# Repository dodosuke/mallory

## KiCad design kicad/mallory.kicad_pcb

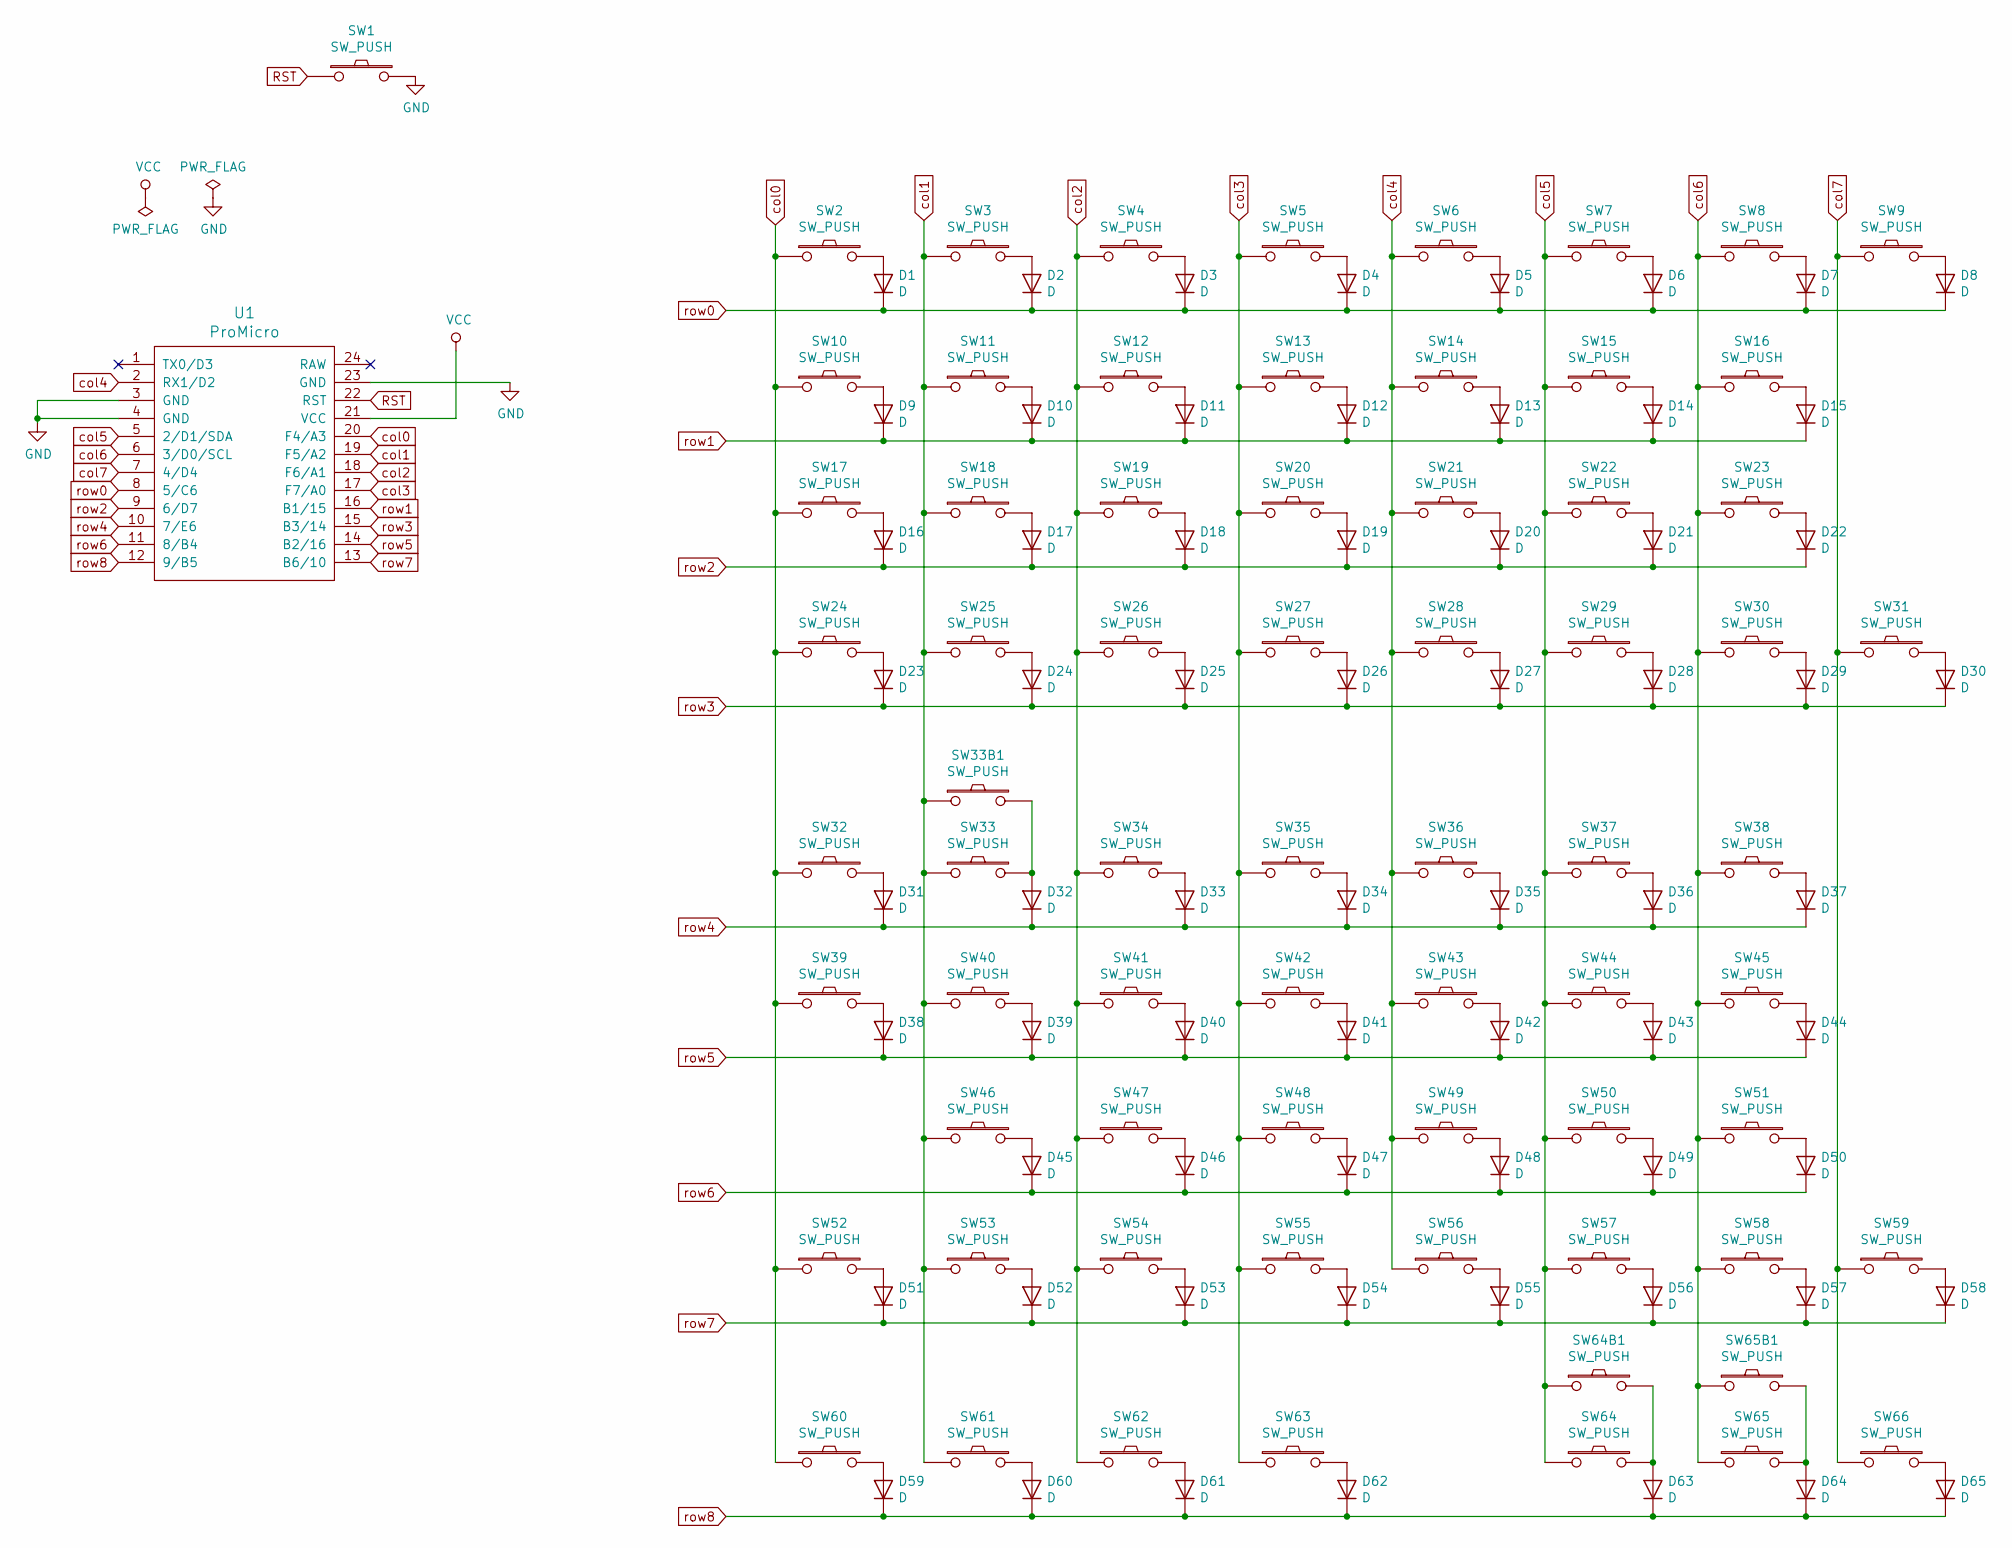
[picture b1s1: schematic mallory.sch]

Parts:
D1, D2, D3, D4, D5, D6, D7, D8, D9, D10, D11, D12, D13, D14, D15, D16, D17, D18, D19, D20, D21, D22, D23, D24, D25, D26, D27, D28, D29, D30, D31, D32, D33, D34, D35, D36, D37, D38, D39, D40, D41, D42, D43, D44, D45, D46, D47, D48, D49, D50, D51, D52, D53, D54, D55, D56, D57, D58, D59, D60, D61, D62, D63, D64, D65: D; D3_TH
SW1: SW_PUSH; ResetSW
SW2, SW3, SW4, SW5, SW6, SW7, SW8, SW9, SW10, SW11, SW12, SW13, SW14, SW15, SW17, SW19, SW20, SW21, SW22, SW23, SW24, SW25, SW26, SW27, SW28, SW29, SW30, SW32, SW33B1, SW34, SW35, SW36, SW37, SW38, SW39, SW40, SW41, SW42, SW43, SW44, SW47, SW48, SW49, SW50, SW51, SW52, SW53, SW54, SW55, SW56, SW57, SW59, SW65: SW_PUSH; MXOnly-1U-NoLED
SW16: SW_PUSH; MXOnly-2U-NoLED
SW18, SW31: SW_PUSH; MXOnly-1.5U-NoLED
SW33, SW58: SW_PUSH; MXOnly-1.75U-NoLED
SW45, SW64: SW_PUSH; MXOnly-2.25U-ReversedStabilizers-NoLED
SW46: SW_PUSH; MXOnly-2.25U-NoLED
SW60, SW62, SW63, SW65B1, SW66: SW_PUSH; MXOnly-1.25U-NoLED
SW61: SW_PUSH; MXOnly-2.75U-ReversedStabilizers-NoLED
SW64B1: SW_PUSH; MXOnly-2U-ReversedStabilizers-NoLED
U1: ProMicro; ProMicro_v3.5

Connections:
GND: SW1.2, U1.3 (GND), U1.4 (GND), U1.23 (GND)
unnamed: D1.2 (A), SW2.2
unnamed: D2.2 (A), SW3.2
unnamed: D3.2 (A), SW4.2
unnamed: D4.2 (A), SW5.2
unnamed: D5.2 (A), SW6.2
unnamed: D6.2 (A), SW7.2
unnamed: D7.2 (A), SW8.2
unnamed: D8.2 (A), SW9.2
unnamed: D9.2 (A), SW10.2
unnamed: D10.2 (A), SW11.2
unnamed: D11.2 (A), SW12.2
unnamed: D12.2 (A), SW13.2
unnamed: D13.2 (A), SW14.2
unnamed: D14.2 (A), SW15.2
unnamed: D15.2 (A), SW16.2
unnamed: D16.2 (A), SW17.2
unnamed: D17.2 (A), SW18.2
unnamed: D18.2 (A), SW19.2
unnamed: D19.2 (A), SW20.2
unnamed: D20.2 (A), SW21.2
unnamed: D21.2 (A), SW22.2
unnamed: D22.2 (A), SW23.2
unnamed: D23.2 (A), SW24.2
unnamed: D24.2 (A), SW25.2
unnamed: D25.2 (A), SW26.2
unnamed: D26.2 (A), SW27.2
unnamed: D27.2 (A), SW28.2
unnamed: D28.2 (A), SW29.2
unnamed: D29.2 (A), SW30.2
unnamed: D30.2 (A), SW31.2
unnamed: D31.2 (A), SW32.2
unnamed: D32.2 (A), SW33.2, SW33B1.2
unnamed: D33.2 (A), SW34.2
unnamed: D34.2 (A), SW35.2
unnamed: D35.2 (A), SW36.2
unnamed: D36.2 (A), SW37.2
unnamed: D37.2 (A), SW38.2
unnamed: D38.2 (A), SW39.2
unnamed: D39.2 (A), SW40.2
unnamed: D40.2 (A), SW41.2
unnamed: D41.2 (A), SW42.2
unnamed: D42.2 (A), SW43.2
unnamed: D43.2 (A), SW44.2
unnamed: D44.2 (A), SW45.2
unnamed: D45.2 (A), SW46.2
unnamed: D46.2 (A), SW47.2
unnamed: D47.2 (A), SW48.2
unnamed: D48.2 (A), SW49.2
unnamed: D49.2 (A), SW50.2
unnamed: D50.2 (A), SW51.2
unnamed: D51.2 (A), SW52.2
unnamed: D52.2 (A), SW53.2
unnamed: D53.2 (A), SW54.2
unnamed: D54.2 (A), SW55.2
unnamed: D55.2 (A), SW56.2
unnamed: D56.2 (A), SW57.2
unnamed: D57.2 (A), SW58.2
unnamed: D58.2 (A), SW59.2
unnamed: D59.2 (A), SW60.2
unnamed: D60.2 (A), SW61.2
unnamed: D61.2 (A), SW62.2
unnamed: D62.2 (A), SW63.2
unnamed: D63.2 (A), SW64.2, SW64B1.2
unnamed: D64.2 (A), SW65.2, SW65B1.2
unnamed: D65.2 (A), SW66.2
RST: SW1.1, U1.22 (RST)
VCC: U1.21 (VCC)
col0: SW2.1, SW10.1, SW17.1, SW24.1, SW32.1, SW39.1, SW52.1, SW60.1, U1.20 (F4/A3)
col1: SW3.1, SW11.1, SW18.1, SW25.1, SW33.1, SW33B1.1, SW40.1, SW46.1, SW53.1, SW61.1, U1.19 (F5/A2)
col2: SW4.1, SW12.1, SW19.1, SW26.1, SW34.1, SW41.1, SW47.1, SW54.1, SW62.1, U1.18 (F6/A1)
col3: SW5.1, SW13.1, SW20.1, SW27.1, SW35.1, SW42.1, SW48.1, SW55.1, SW63.1, U1.17 (F7/A0)
col4: SW6.1, SW14.1, SW21.1, SW28.1, SW36.1, SW43.1, SW49.1, SW56.1, U1.2 (RX1/D2)
col5: SW7.1, SW15.1, SW22.1, SW29.1, SW37.1, SW44.1, SW50.1, SW57.1, SW64.1, SW64B1.1, U1.5 (2/D1/SDA)
col6: SW8.1, SW16.1, SW23.1, SW30.1, SW38.1, SW45.1, SW51.1, SW58.1, SW65.1, SW65B1.1, U1.6 (3/D0/SCL)
col7: SW9.1, SW31.1, SW59.1, SW66.1, U1.7 (4/D4)
row0: D1.1 (K), D2.1 (K), D3.1 (K), D4.1 (K), D5.1 (K), D6.1 (K), D7.1 (K), D8.1 (K), U1.8 (5/C6)
row1: D9.1 (K), D10.1 (K), D11.1 (K), D12.1 (K), D13.1 (K), D14.1 (K), D15.1 (K), U1.16 (B1/15)
row2: D16.1 (K), D17.1 (K), D18.1 (K), D19.1 (K), D20.1 (K), D21.1 (K), D22.1 (K), U1.9 (6/D7)
row3: D23.1 (K), D24.1 (K), D25.1 (K), D26.1 (K), D27.1 (K), D28.1 (K), D29.1 (K), D30.1 (K), U1.15 (B3/14)
row4: D31.1 (K), D32.1 (K), D33.1 (K), D34.1 (K), D35.1 (K), D36.1 (K), D37.1 (K), U1.10 (7/E6)
row5: D38.1 (K), D39.1 (K), D40.1 (K), D41.1 (K), D42.1 (K), D43.1 (K), D44.1 (K), U1.14 (B2/16)
row6: D45.1 (K), D46.1 (K), D47.1 (K), D48.1 (K), D49.1 (K), D50.1 (K), U1.11 (8/B4)
row7: D51.1 (K), D52.1 (K), D53.1 (K), D54.1 (K), D55.1 (K), D56.1 (K), D57.1 (K), D58.1 (K), U1.13 (B6/10)
row8: D59.1 (K), D60.1 (K), D61.1 (K), D62.1 (K), D63.1 (K), D64.1 (K), D65.1 (K), U1.12 (9/B5)

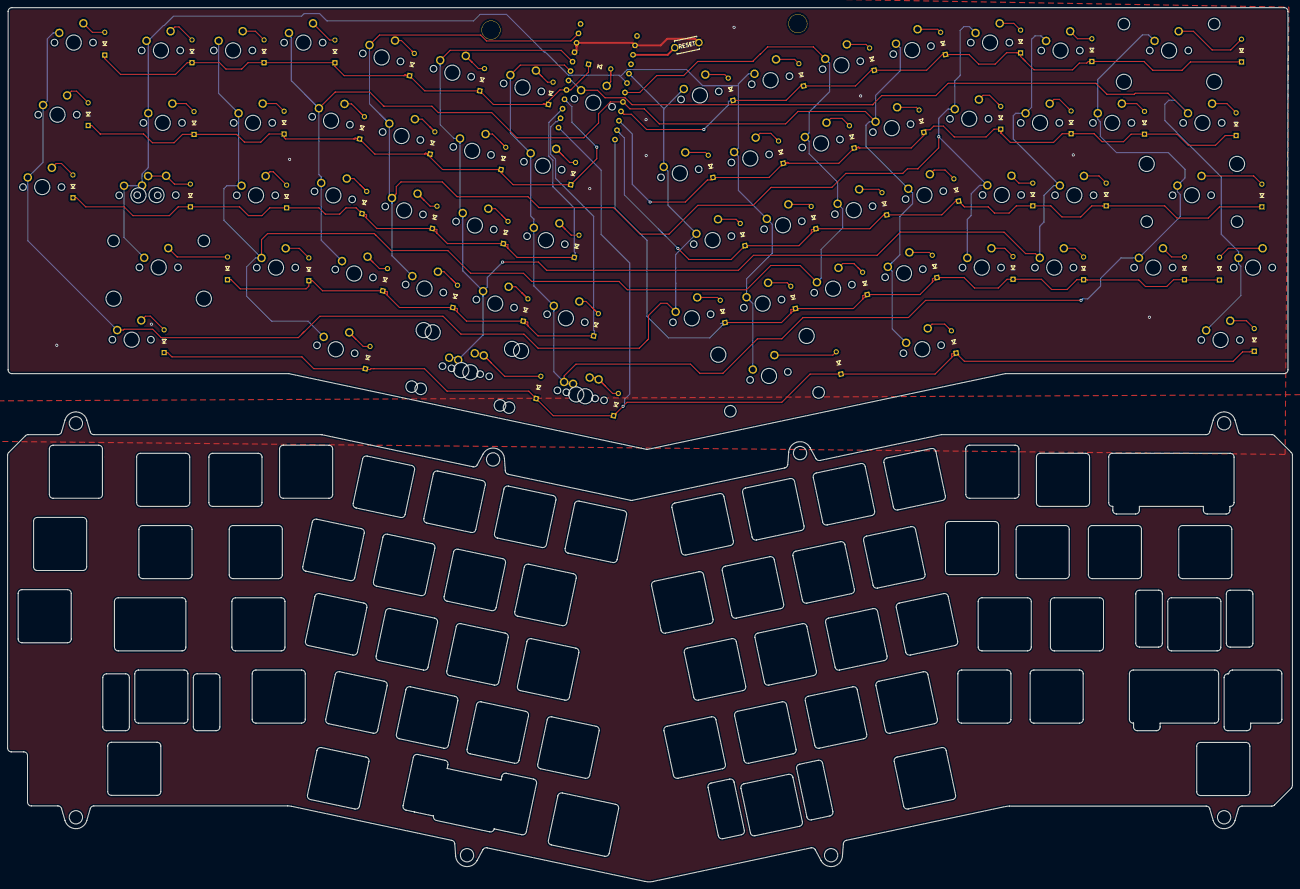
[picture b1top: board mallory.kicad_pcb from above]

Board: 2 copper layers, 338.8 x 230.5 mm, 137 parts (1 on the bottom side), 84 nets.

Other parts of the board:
Ref01: Val01; HOLE
Ref02: Val02; HOLE

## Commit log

2019-09-12 add gitignore
2019-09-12 Add openscad
2019-09-12 Update cases
2019-09-23 Update case
2019-09-26 Add 2D plate
2019-09-27 Update: refactoring
